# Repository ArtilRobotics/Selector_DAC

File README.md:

# Selector_DAC
A PCB to convert the signal from 2 selector devices 4 &amp; 5 ways with 24V input to proportional out from 0 to 10V DC.

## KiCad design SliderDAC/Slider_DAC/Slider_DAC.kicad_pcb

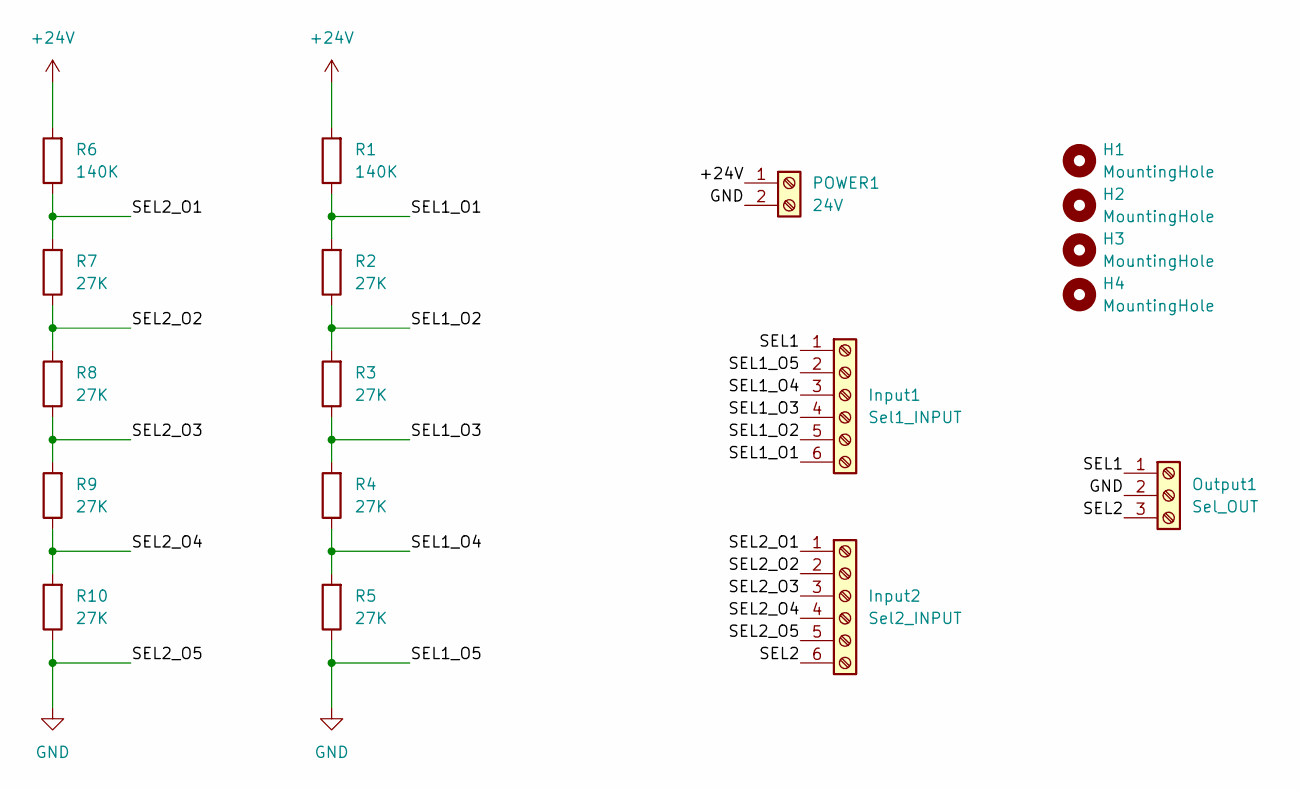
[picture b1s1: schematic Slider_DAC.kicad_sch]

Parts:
H1, H3, H4: MountingHole; MountingHole_3.2mm_M3
H2: MountingHole
Input1: Sel1_INPUT
Input2: Sel2_INPUT; TerminalBlock_bornier-6_P5.08mm
Output1: Sel_OUT; TerminalBlock_bornier-3_P5.08mm
POWER1: 24V; TerminalBlock_bornier-2_P5.08mm
R1, R6: 140K; R_Axial_DIN0207_L6.3mm_D2.5mm_P7.62mm_Horizontal
R2, R3, R4, R5, R7, R8, R9, R10: 27K; R_Axial_DIN0207_L6.3mm_D2.5mm_P7.62mm_Horizontal

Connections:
+24V: POWER1.1, R1.2, R6.2
/SEL1: Input1.1, Output1.1
/SEL1_O1: Input1.6, R1.1, R2.2
/SEL1_O2: Input1.5, R2.1, R3.2
/SEL1_O3: Input1.4, R3.1, R4.2
/SEL1_O4: Input1.3, R4.1, R5.2
/SEL2: Input2.6, Output1.3
/SEL2_O1: Input2.1, R6.1, R7.2
/SEL2_O2: Input2.2, R7.1, R8.2
/SEL2_O3: Input2.3, R8.1, R9.2
/SEL2_O4: Input2.4, R9.1, R10.2
GND: Input1.2, Input2.5, Output1.2, POWER1.2, R5.1, R10.1

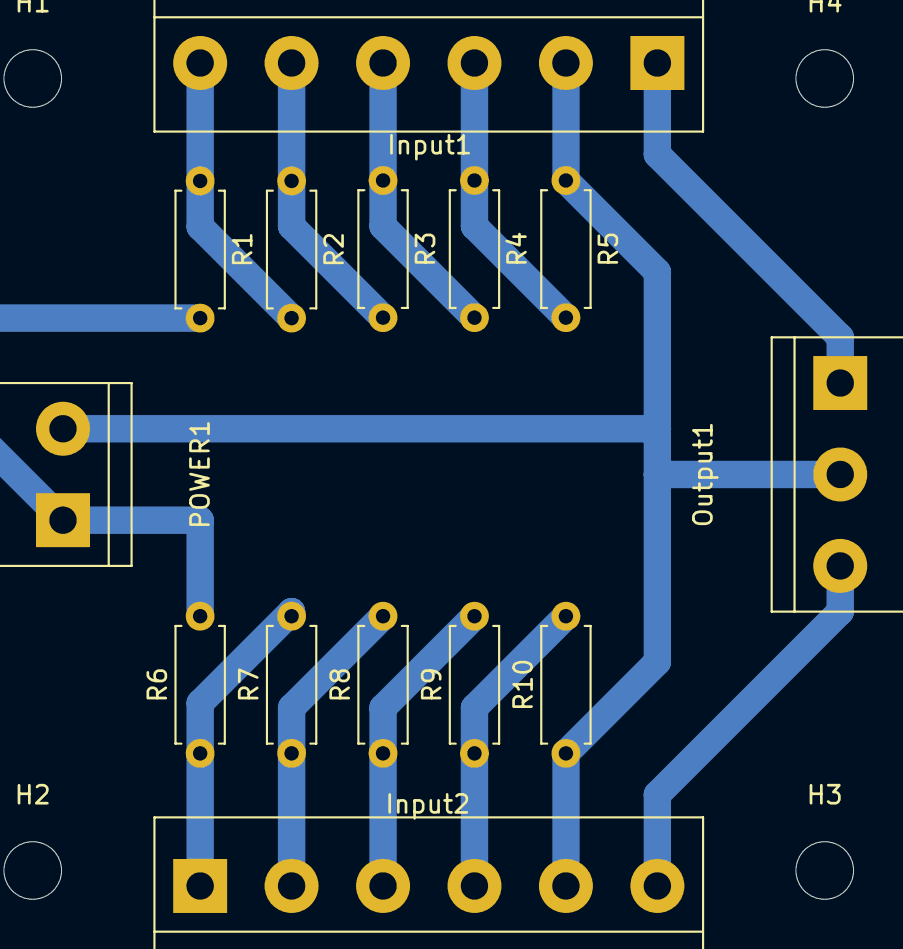
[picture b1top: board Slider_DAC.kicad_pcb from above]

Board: 2 copper layers, 18 parts (0 on the bottom side), 12 nets.

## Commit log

2022-11-02 SUBIDA DE ARCHIVOS
2022-11-02 Git Ignore File
2022-11-02 deletebackups
2022-11-02 rebase without kicad backups
